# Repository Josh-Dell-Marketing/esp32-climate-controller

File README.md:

# Climate Controller (two ESP32 boards)

Holds a temperature set point and a humidity set point by switching 4 relays: **fan, heater, humidifier, compressor**. The fan speed is set with a 0-10 V signal, and the fan's tach output is watched for a fan fault.

There are two boards joined by a serial cable:

- **Mainboard**: ESP32 NodeMCU WROOM-32 DevKit. Runs the control rules. It reads the AHT20 + BMP280 sensor, switches the relay board, drives the PWM to 0-10 V converter for the fan speed, and reads the fan tach. It keeps the settings in flash, and carries on controlling if the Controller is unplugged.
- **Controller**: ESP32-C3 SuperMini. The user interface: a 1.3" OLED (DST-013) and two rotary encoders with push switches. It shows the readings, the set points, what is running and any fault, and sends your changes to the Mainboard.

More documents:

- The project plan, the control rules and the phases are in **[PLAN.md](PLAN.md)**.
- Picking up the project? Start with **[CLAUDE.md](CLAUDE.md)**.
- Wiring both boards on breadboards and flashing them from Windows 11: **[docs/BENCH_SETUP.md](docs/BENCH_SETUP.md)**.
- **[hardware/](hardware/README.md)** has the relay carrier PCB (KiCad 10), its simulations and a 3D-printable case. These are the Phase 1 **ESP8266** design and do not fit the new Mainboard. They are kept for reference.

**Mains:** a compressor needs a contactor, and a heater needs its own thermal cut-out. See PLAN.md section 1.

## Mainboard pinout (ESP32 NodeMCU WROOM-32)

```
                      +---------------------+
                  EN  | o                 o |  GPIO23
              GPIO36  | o                 o |  GPIO22 ------> sensor SCL
              GPIO39  | o                 o |  GPIO1 (TX0, USB)
 fan tach --> GPIO34  | o                 o |  GPIO3 (RX0, USB)
              GPIO35  | o                 o |  GPIO21 <-----> sensor SDA
 IN3 hum  <-- GPIO32  | o                 o |  GPIO19
 IN4 comp <-- GPIO33  | o                 o |  GPIO18
 fan PWM  <-- GPIO25  | o                 o |  GPIO5
 IN1 fan  <-- GPIO26  | o                 o |  GPIO17 (TX2) ---> Controller RX (GPIO20)
 IN2 heat <-- GPIO27  | o                 o |  GPIO16 (RX2) <--- Controller TX (GPIO21)
              GPIO14  | o                 o |  GPIO4 ----------> RS-485 DE/RE (later)
              GPIO12  | o                 o |  GPIO2
              GPIO13  | o                 o |  GPIO15
                 GND  | o                 o |  GND
 5 V in/out      VIN  | o                 o |  3V3 ------------> sensor VIN, tach pull-up
                      +-------[USB]---------+
```

This is the common 30-pin board. The 38-pin DevKitC has the same GPIOs in a different order, so wire by the GPIO numbers printed on your board.

| GPIO | Connects to | Notes |
|---|---|---|
| 26 | Relay board IN1: **Fan** | |
| 27 | Relay board IN2: **Heater** | |
| 32 | Relay board IN3: **Humidifier** | |
| 33 | Relay board IN4: **Compressor** | |
| VIN (5 V), GND | Relay board VCC, GND | |
| 21 | Sensor SDA | AHT20 (0x38) + BMP280 (0x76/0x77), I2C at 100 kHz |
| 22 | Sensor SCL | |
| 3V3, GND | Sensor VIN, GND | |
| 25 | PWM to 0-10 V converter: PWM input | 1 kHz. Converter GND to Mainboard GND |
| 34 | Fan tach | Input only. **Fit a 10 kΩ pull-up to 3V3** (never 5 V), plus 1 kΩ in series and 10 nF to GND at the pin |
| 17 (TX2) | Controller RX (GPIO 20) | Link, 115200 baud |
| 16 (RX2) | Controller TX (GPIO 21) | |
| 4 | MAX485 DE + /RE (when RS-485 is fitted) | High while sending. Driven even on plain UART, where it is harmless |
| VIN, GND | Controller 5V, GND (in the link cable) | Powers the Controller |

Pins to leave alone: GPIO 0, 2, 5, 12 and 15 (they decide how the chip boots), 6 to 11 (flash), 1 and 3 (USB serial).

**Relay board:** most cheap 4-relay boards switch on when IN is LOW (`RELAY_ACTIVE_LOW = true` in `src/mainboard/config.h`). If a relay will not switch off, or its LED glows faintly, the 3.3 V signal is not quite high enough for the 5 V board. Remove the JD-VCC jumper, power JD-VCC from 5 V, and power VCC from the ESP32's 3V3.

**Fan:** the converter output goes to the fan's 0-10 V input, and its output ground to the fan's 0-10 V reference ground. Check that the fan's 0-10 V input and tach are SELV (isolated from mains) before connecting them. Some converters need a PWM signal of 5 V or more: if yours does not respond to 3.3 V, add a transistor or level shifter. Calibrate it with a meter and set `FAN_PWM_DUTY_AT_0V` / `FAN_PWM_DUTY_AT_10V` in `src/mainboard/config.h`.

## Controller pinout (ESP32-C3 SuperMini)

| GPIO | Connects to | Notes |
|---|---|---|
| 8 | OLED SDA | Strapping pin, held high by the I2C pull-ups |
| 9 | OLED SCK | Strapping pin (BOOT button) |
| 3V3, GND | OLED VDD, GND | |
| 0 | Encoder 1 A (CLK) | Encoder 1: temperature, mode |
| 1 | Encoder 1 B (DT) | |
| 3 | Encoder 1 push (SW) | |
| 4 | Encoder 2 A (CLK) | Encoder 2: humidity, menu |
| 5 | Encoder 2 B (DT) | |
| 10 | Encoder 2 push (SW) | |
| GND | Encoder common (and the switch's other side) | Internal pull-ups are used |
| 21 | Mainboard RX2 (GPIO 16) | Link |
| 20 | Mainboard TX2 (GPIO 17) | |
| 7 | MAX485 DE + /RE (when RS-485 is fitted) | |
| 5V, GND | Mainboard VIN, GND (in the link cable) | |

If your encoders are on a module with a "+" pin (such as the KY-040), connect "+" to **3V3**, not 5 V. GPIO 18/19 are the USB port. GPIO 2 and 6 are spare.

## Link cable

For now this is plain UART over a short cable (4 cores: 5 V, GND, TX, RX, with TX and RX crossed over). For the planned ~10 m run, fit a MAX485-type RS-485 module at each end and use a twisted pair for A/B:

- Each ESP32's TX goes to DI, RX to RO, and the DE and /RE pins (tied together) to GPIO 4 on the Mainboard and GPIO 7 on the Controller. A to A, B to B.
- **The MAX485 is a 5 V chip, and its RO output is 5 V, which the ESP32 inputs cannot take.** Use a 3.3 V part (MAX3485, SP3485) powered from 3V3, or put a divider (for example 1 kΩ / 2 kΩ) between RO and the ESP32 RX pin.
- Fit 120 Ω termination across A/B at both ends of a long cable. Most modules have it on board.
- No firmware change is needed: the link only ever has one side sending at a time, and the DE pin is already driven.

## Build and upload

1. Open this folder in VS Code with the PlatformIO extension.
2. Plug in one board, and pick its environment:
   - Mainboard: `pio run -e mainboard -t upload`
   - Controller: `pio run -e controller -t upload`
3. `pio run` (no `-e`) builds both.
4. Serial monitor at 115200: `pio device monitor -e mainboard` (or `-e controller`).

With both boards plugged in at once, say which port to use. For example, on Windows:

```bash
pio run -e mainboard -t upload --upload-port COM5
```

On Linux the ports are names like `/dev/ttyUSB0` (Mainboard) and `/dev/ttyACM0` (Controller).

The SuperMini flashes over its own USB port. If it will not connect, hold **BOOT**, tap **RESET**, release BOOT and upload again. After that, press RESET to start the new firmware.

The WROOM-32 DevKit needs a CP210x or CH340 USB driver on Windows, depending on the board. If an upload hangs at "Connecting...", hold its **BOOT** button until the upload starts.

## Using the Controller

**Home screen:** temperature and humidity (large), the set points, the mode, the loads that are running, and a bottom line with the fan speed and RPM, the pressure, or a fault.

| Control | What it does |
|---|---|
| Turn encoder 1 | Temperature set point (0.1 °C steps) |
| Push encoder 1 | Next mode: Off, Auto, Manual |
| Turn encoder 2 | Humidity set point (1 % steps) |
| Long-push encoder 2 | Settings menu |

A value you are changing is shown inverted. It is sent to the Mainboard once the knob has been still for 1 s, and goes back to normal when the Mainboard accepts it.

**Settings menu:** turn encoder 2 to choose an item, and turn encoder 1 to change it. Push either encoder on **Clear fan fault** or **Exit**. Long-push encoder 2 to go back, or leave it alone for 60 s. The items are:

- Bands and the fan settings: fan mode, speed, run-on, and the fan fault RPM (0 turns the check off), spin-up and delay.
- Compressor times and sensor offsets.
- The manual relay switches (only shown in Manual mode).
- Real or simulated sensor. In Sim, the simulated temperature, humidity, "room reacts" and sensor fault are shown too.

**Faults:** SENSOR FAULT and FAN FAULT take over the screen until you push either encoder. They then stay on the bottom line while they last. A fan fault is latched: clear it from the menu once the fan is working again. If the Controller hears nothing from the Mainboard for 5 s it shows **NO LINK TO MAINBOARD**. The Mainboard keeps controlling with its saved settings.

The simulated sensor is never saved: the Mainboard always starts on the real sensor after a reset.

## Mainboard serial commands (115200 baud, USB)

For bench testing without the Controller. Type `help` for the list.

```
status | settings | help
mode off|auto|manual
sensor real|sim
temp <C> | hum <%RH>        simulated reading (switches to the simulated sensor)
react on|off | fault on|off
relay <1-4> on|off           Manual mode only
clearfault
set <name> <value>           any name from "settings", e.g. set tempset 21.5
```

## Files

```
PLAN.md                        Project plan, control rules, pin plan, phases
platformio.ini                 Build environments: mainboard, controller
include/link_protocol.h        Link messages, shared by both firmwares
src/mainboard/main.cpp         Mainboard: relays, fan, link, serial commands
src/mainboard/climate_control.*  Control rules and fan fault (plain C++, no Arduino code)
src/mainboard/sensor.*         AHT20 + BMP280
src/mainboard/fan.*            Fan PWM (0-10 V) and tach
src/mainboard/storage.*        Saves settings to flash
src/mainboard/sim_room.h       Simulated sensor and room
src/mainboard/config.h         Mainboard pins and timings
src/controller/main.cpp        Controller: display, menus, link
src/controller/input.h         Encoders and push buttons
src/controller/config.h        Controller pins and timings
tools/host-test/               Tests of the control rules and link framing, run on a PC
```

The control rules can be tested on a PC without a board (needs `g++`):

```bash
g++ -std=c++17 -Isrc/mainboard -Iinclude tools/host-test/test_control.cpp src/mainboard/climate_control.cpp -o test_control && ./test_control
```

The Phase 1 firmware (ESP8266, web page, WiFi, OTA) was removed. The last commit with it is `65d825e`.

## License

- Firmware, scripts and documentation: [MIT](LICENSE).
- Hardware (everything in `hardware/`: the KiCad design files, generator scripts, simulations and case CAD): [CERN-OHL-P-2.0](hardware/LICENSE), the permissive CERN Open Hardware Licence. You may use, change, make and sell it. Keep the licence notice with any copies of the design files.

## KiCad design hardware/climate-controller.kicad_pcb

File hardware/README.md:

# Climate Controller – Relay Carrier PCB

> **Status: Phase 1 design, on hold.** This board was designed for the original single-board version (ESP8266 NodeMCU v2 + SHT31-D). The project now uses an ESP32 WROOM-32 Mainboard with an AHT20 + BMP280 sensor, a PWM to 0-10 V fan speed output, a fan tach input and a link to a separate Controller board (see [PLAN.md](../PLAN.md)). This PCB does not fit that, and the `nodemcuv2-pcb` firmware environment it needs has been removed. The last commit with that firmware is `65d825e`. Whether to rework this board for the ESP32 or to use an off-the-shelf relay board is an open item in PLAN.md Phase 5. Everything below describes the board as designed.

A 2-layer, 90 × 86 mm through-hole carrier board for the climate controller. It has:

- 4 × SRD-05VDC-SL-C relays: fan, humidifier, compressor and heater.
- A plug-in NodeMCU v2 (ESP8266), so you keep USB programming and the existing firmware pins.
- A JST connector for the SHT31-D sensor.
- 5 V DC input with a resettable fuse and reverse-polarity protection.

Everything here is generated from **`gen/design.py`**: parts, values, connections and placement. Change the design there and rebuild. Don't hand-edit the `.kicad_sch` / `.kicad_pcb` and then rebuild, because the rebuild overwrites them. You can still open and inspect them in KiCad 10.

| File | What it is |
|---|---|
| `climate-controller.kicad_pro/.kicad_sch/.kicad_pcb` | The KiCad 10 project. Open the `.kicad_pro` in KiCad |
| `climate-controller.kicad_dru` | Custom DRC rules: mains clearance and creepage |
| `lib/` | Project symbol and footprint for the NodeMCU, plus a simple 3D model |
| `gen/` | Generator: `design.py` (single source), `make_sch.py`, `make_pcb.py`, `router.py`, `make_pro.py` |
| `build.ps1` | Rebuilds everything and runs ERC/DRC. `-Fab` also writes manufacturing files |
| `sim/` | SPICE simulations (ngspice): `SIM_REPORT.md`, plots, `run_sim.py` |
| `case/` | 3D-printable enclosure (CadQuery): see `case/CASE.md` |
| `build/` | Generated: renders, ERC/DRC reports, `fab/` (Gerbers, drill, BOM, PDFs, STEP). Not in git |

## Rebuild and check

```
powershell -ExecutionPolicy Bypass -File hardware\build.ps1 -Fab
```

This takes about 1 minute and needs KiCad 10 in `C:\Program Files\KiCad\10.0`. It writes the schematic, runs ERC, places and routes the PCB, pours ground, runs DRC with the schematic-parity check, renders images, and exports the manufacturing files.

Results of the current design:

| Check | Result |
|---|---|
| ERC | 0 errors, 0 warnings |
| DRC | 0 errors, 0 unconnected items, 0 schematic/PCB differences. The 91 warnings are silkscreen cosmetics, such as text overlapping outlines |
| Mains → low-voltage clearance (rule ≥ 3.0 mm) | **3.70 mm** minimum |
| Mains → low-voltage creepage (rule ≥ 4.0 mm) | **4.83 mm** minimum, using routed slots around each relay's COM pin |
| Mains → mains, between COM/NO/NC (rule ≥ 2.0 mm) | 2.78 mm minimum. This is set by the 5.08 mm terminal pitch |
| Mains → mounting screws (rule ≥ 3.0 mm) | 5.12 mm minimum |

Each minimum was measured with KiCad's DRC engine. I also checked that the rules really are enforced: setting them to 20 mm on a scratch copy produced hundreds of violations. KiCad silently ignores a rule condition written as `!B.hasNetclass('Mains')`, so `gen/make_pro.py` uses `B.NetClass != 'Mains'`.

## Circuit

- **Relay driver (×4):** GPIO → 1 kΩ → BC337-40, with 4.7 kΩ base-to-emitter so the relay stays off while the ESP8266 boots. The coil runs from +5 V with a 1N4148 flyback diode. A red LED + 1 kΩ across the coil shows when the relay is on. **The relays are active HIGH**, so the firmware must have `RELAY_ACTIVE_LOW = false` (this was the Phase 1 `nodemcuv2-pcb` build).
- **Channels, left to right:** 1 FAN (D0), 2 HUMIDIFIER (D5), 3 COMPRESSOR (D6), 4 HEATER (D7). These match the Phase 1 (ESP8266) firmware pins. The order follows the NodeMCU pin order so the traces don't cross.
- **Outputs:** each relay has a 3-way screw terminal, NC / COM / NO from left to right.
- **Power:** J1 5 V DC → F1 PTC fuse → D5 1N5819 (reverse protection) → +5V → relays and NodeMCU VIN. **Use a 5.1–5.25 V, ≥ 1 A supply.** The fuse and diode drop about 0.45 V, and the NodeMCU's 3.3 V regulator needs about 4.4 V in. The simulation shows a bare 5.00 V supply leaves only 70 mV of headroom on the regulator input.
- **Sensor:** J6 (JST-XH 4-pin) is wired 3V3, GND, SCL, SDA, matching most SHT31-D breakouts. R14/R15 are 4.7 kΩ pull-ups. J7 is a spare I2C header. Run I2C at 100 kHz.
- **USB:** with the NodeMCU on USB and no 5 V supply, the relays still work, powered through the NodeMCU's own diode. D5 stops that power flowing back into J1. With all 4 relays on, peaks reach about 0.57 A, which is over a USB 2.0 port's 500 mA. Use the 5 V supply for anything more than a quick test.

## Simulation summary (`sim/SIM_REPORT.md`)

These were run in ngspice with manufacturer SPICE models. A coil inductance of 50–500 mH was swept, and the results don't depend on it.

| Check | Result |
|---|---|
| GPIO current | 2.4 mA (limit 12 mA) |
| Transistor Vce(sat) | 55 mV worst case |
| Coil voltage at 4.5 V supply | 4.45 V (must-operate 3.75 V) |
| Turn-off spike | 5.8 V with the flyback diode (about 50 V and avalanche without it) |
| Relay held off during boot | Yes, with the 4.7 kΩ pull-downs, even with a 30 kΩ internal pull-up enabled (10 kΩ failed that case) |
| +5 V rail at 5.0 V input | ≥ 4.47 V (typical diode). With a 4.75 V input the 3.3 V regulator is short of headroom, hence the 5.1–5.25 V supply |
| I2C rise time | 0.4–0.8 µs at 100–200 pF (passes 100 kHz). For a long sensor cable (≈400 pF), fit 2.2 kΩ pull-ups |
| Relay contact traces | 2 mm on both layers: about 5 °C rise at 5 A, 16 °C at 8 A. **This board is rated 5 A per channel** |

## Ordering the PCB

Upload `build/fab/climate-controller-gerbers.zip` to any PCB maker (for example JLCPCB, PCBWay or Aisler) with these settings:

- 2 layers, FR4, 1.6 mm, 1 oz copper (2 oz is optional), HASL or ENIG, any colour.
- **Board outline includes routed slots.** Four U-shaped 1 mm slots around the relay COM pins are on the Edge.Cuts layer. Most makers mill these at no extra cost; check that they appear in the maker's Gerber preview.

## Parts (BOM)

The full BOM is in `build/fab/climate-controller-bom.csv`.

| Refs | Qty | Part | Notes |
|---|---|---|---|
| K1–K4 | 4 | Songle SRD-05VDC-SL-C | 5 V coil, 10 A contacts. **5 A max on this board** |
| Q1–Q4 | 4 | BC337-40, TO-92 | Pinout C-B-E |
| D1–D4 | 4 | 1N4148 | Flyback, cathode band to +5V |
| D5 | 1 | 1N5819 | Reverse protection |
| D6–D9 / D10 | 4 / 1 | 3 mm LED, red / green | Relay on / power |
| R1–R4, R9–R13 | 9 | 1 kΩ ¼ W | |
| R5–R8, R14, R15 | 6 | 4.7 kΩ ¼ W | |
| C1 | 1 | 470 µF 10 V electrolytic, 8 mm, 3.5 mm pitch | |
| C2, C3 | 2 | 100 nF ceramic, 5 mm pitch | |
| F1 | 1 | Bourns MF-RHT100 PTC (about 1 A hold) | Check the hold current on the datasheet before ordering. Any radial PTC of about 1 A hold, ≥ 6 V, with 5.1 mm pitch fits |
| J1 | 1 | Phoenix MKDS 1,5/2-5,08 (or any 5.08 mm 2-way screw terminal) | |
| J2–J5 | 4 | Phoenix MKDS 1,5/3-5,08 (or any 5.08 mm 3-way screw terminal) | Wire entry faces the board edge |
| J6 | 1 | JST B4B-XH-A + housing XHP-4 + crimps | Sensor cable |
| J7 | 1 | 1×4 2.54 mm pin header | Optional |
| U1 | 2 | 1×15 2.54 mm female header | The NodeMCU v2 plugs in here |
| – | 4 | M3 screws | Mounting |

## Assembly

1. **Check your NodeMCU first.** This board is for the v2 "Amica" (CP2102 USB chip) with **22.86 mm (0.9 in) between the pin rows**. The wider "LoLin v3" (27.9 mm) will not fit.
2. Solder the lowest parts first: resistors, diodes, then LEDs and transistors (flat face as on the silkscreen), C2/C3, the sockets, C1, F1, the terminals and JST connector, and finally the relays.
3. **Bring-up, without the NodeMCU:**
   - Apply 5.1 V to J1. The green LED should light.
   - Check about 4.6–4.7 V between the +5V and GND pins of the sockets (U1 pin 15 VIN and pin 14 GND).
   - Touch a 1 kΩ resistor from 3.3 V to each relay's base resistor (R1–R4, GPIO side). The relay should click and its red LED light.
4. Plug in the NodeMCU with the USB end at the board edge. Flash the Phase 1 firmware (commit `65d825e`) with `pio run -e nodemcuv2-pcb -t upload`.
5. Test each relay in the web page's **Manual** mode before connecting any load.

## Safety

- The relay contact area (top of the board, "DANGER MAINS") can be at mains voltage. Mains wiring must be done by a competent person, in an earthed or double-insulated enclosure, with suitable fusing on each load.
- 5 A per channel. Drive the **compressor through a contactor** (AC-3 rated), and do the same for any heater over about 1 kW. Fit the heater's own thermal cut-out.
- A 3D-printed case is fine for development. For a permanent mains installation, use a flame-retardant (UL94 V-0) material or a commercial enclosure.

## License

The hardware design in this folder is licensed under the [CERN Open Hardware Licence Version 2 – Permissive](LICENSE) (CERN-OHL-P-2.0). Copyright (c) 2026 Josh-Dell-Marketing and contributors.

Third-party material used in the design keeps its own terms:
- Symbols, footprints and 3D models from the KiCad libraries (embedded in the `.kicad_sch` / `.kicad_pcb` and referenced by the STEP export) are from the KiCad Libraries Team, under CC-BY-SA 4.0 with an exception that allows them to be used in designs under any licence.
- The SPICE models in `sim/models/` come from the manufacturers' published models (NXP/Nexperia BC337-40, onsemi 1N4148 and 1N5819), as noted in each file. They are included for simulation only.

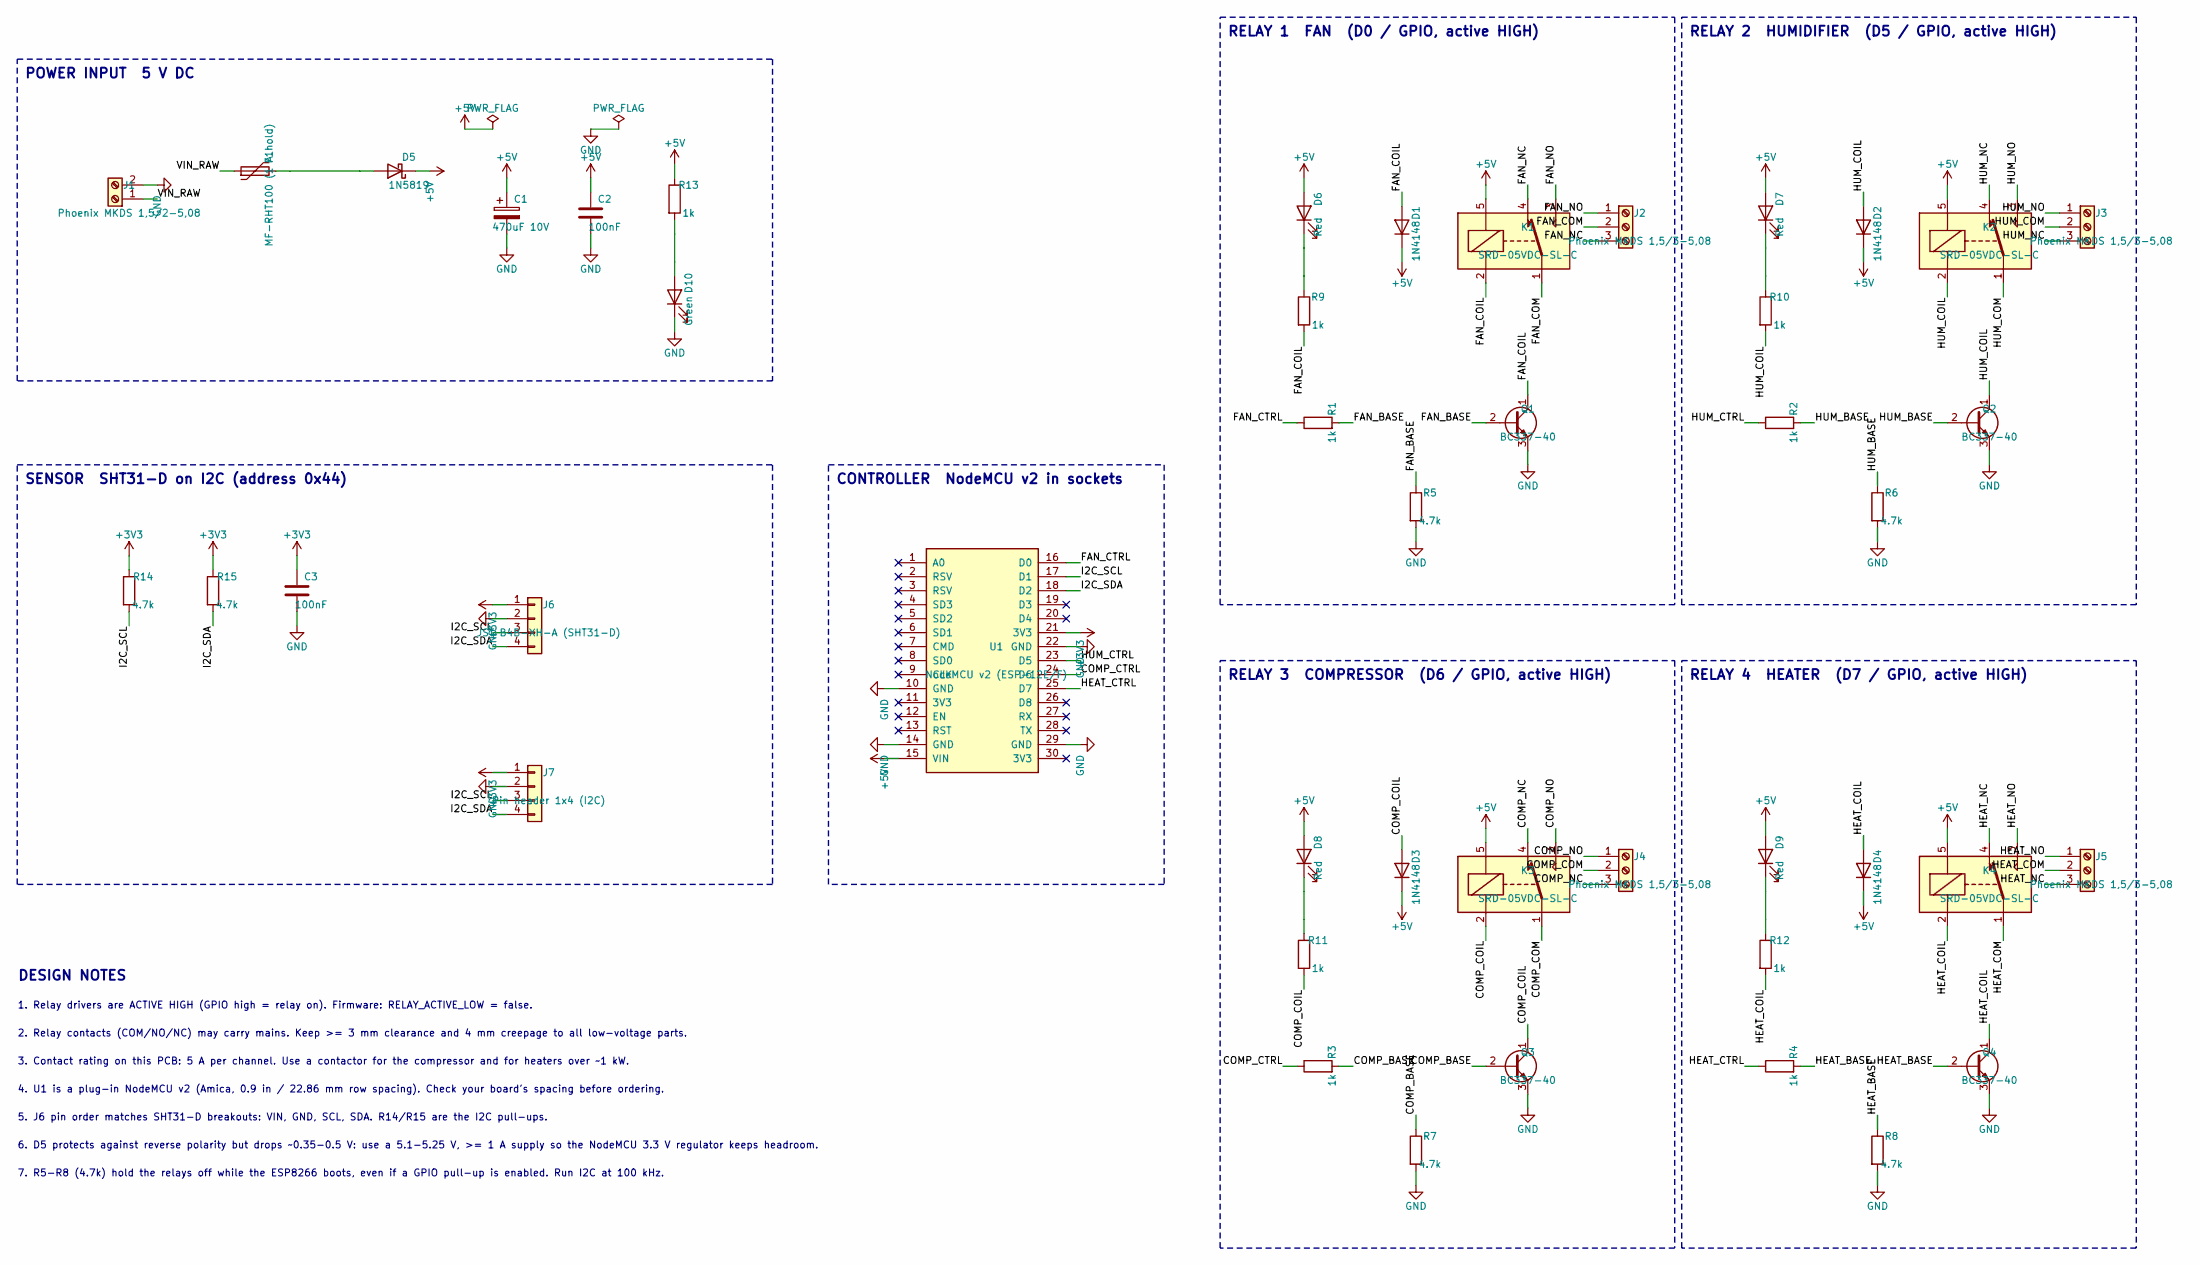
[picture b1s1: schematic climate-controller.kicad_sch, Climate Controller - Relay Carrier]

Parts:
C1: 470uF 10V; CP_Radial_D8.0mm_P3.50mm
C2, C3: 100nF; C_Disc_D5.0mm_W2.5mm_P5.00mm
D1, D2, D3, D4: 1N4148; D_DO-35_SOD27_P7.62mm_Horizontal
D5: 1N5819; D_DO-41_SOD81_P10.16mm_Horizontal
D6, D7, D8, D9: Red; LED_D3.0mm
D10: Green; LED_D3.0mm
F1: MF-RHT100 (1 A hold); Fuse_Bourns_MF-RHT100
J1: Phoenix MKDS 1,5/2-5,08; TerminalBlock_Phoenix_MKDS-1,5-2-5.08_1x02_P5.08mm_Horizont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
J2, J3, J4, J5: Phoenix MKDS 1,5/3-5,08; TerminalBlock_Phoenix_MKDS-1,5-3-5.08_1x03_P5.08mm_Horizont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
J6: JST B4B-XH-A (SHT31-D); JST_XH_B4B-XH-A_1x04_P2.50mm_Vertical
J7: Pin header 1x4 (I2C); PinHeader_1x04_P2.54mm_Vertical
K1, K2, K3, K4: SRD-05VDC-SL-C; Relay_SPDT_SANYOU_SRD_Series_Form_C
Q1, Q2, Q3, Q4: BC337-40; TO-92_Inline_Wide
R1, R2, R3, R4, R9, R10, R11, R12, R13: 1k; R_Axial_DIN0207_L6.3mm_D2.5mm_P7.62mm_Horizontal
R5, R6, R7, R8, R14, R15: 4.7k; R_Axial_DIN0207_L6.3mm_D2.5mm_P7.62mm_Horizontal
U1: NodeMCU v2 (ESP-12E/F); NodeMCU_v2_Socket

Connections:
+3V3: C3.1, J6.1, J7.1, R14.1, R15.1, U1.21 (3V3)
+5V: C1.1, C2.1, D1.1 (K), D2.1 (K), D3.1 (K), D4.1 (K), D5.1 (K), D6.2 (A), D7.2 (A), D8.2 (A), D9.2 (A), K1.5, K2.5, K3.5, K4.5, R13.1, U1.15 (VIN)
/COMP_BASE: Q3.2 (B), R3.2, R7.1
/COMP_COIL: D3.2 (A), K3.2, Q3.1 (C), R11.2
/COMP_COM: J4.2, K3.1
/COMP_CTRL: R3.1, U1.24 (D6)
/COMP_NC: J4.3, K3.4
/COMP_NO: J4.1, K3.3
/FAN_BASE: Q1.2 (B), R1.2, R5.1
/FAN_COIL: D1.2 (A), K1.2, Q1.1 (C), R9.2
/FAN_COM: J2.2, K1.1
/FAN_CTRL: R1.1, U1.16 (D0)
/FAN_NC: J2.3, K1.4
/FAN_NO: J2.1, K1.3
/HEAT_BASE: Q4.2 (B), R4.2, R8.1
/HEAT_COIL: D4.2 (A), K4.2, Q4.1 (C), R12.2
/HEAT_COM: J5.2, K4.1
/HEAT_CTRL: R4.1, U1.25 (D7)
/HEAT_NC: J5.3, K4.4
/HEAT_NO: J5.1, K4.3
/HUM_BASE: Q2.2 (B), R2.2, R6.1
/HUM_COIL: D2.2 (A), K2.2, Q2.1 (C), R10.2
/HUM_COM: J3.2, K2.1
/HUM_CTRL: R2.1, U1.23 (D5)
/HUM_NC: J3.3, K2.4
/HUM_NO: J3.1, K2.3
/I2C_SCL: J6.3, J7.3, R14.2, U1.17 (D1)
/I2C_SDA: J6.4, J7.4, R15.2, U1.18 (D2)
/VIN_RAW: F1.1, J1.1
GND: C1.2, C2.2, C3.2, D10.1 (K), J1.2, J6.2, J7.2, Q1.3 (E), Q2.3 (E), Q3.3 (E), Q4.3 (E), R5.2, R6.2, R7.2, R8.2, U1.10 (GND), U1.14 (GND), U1.22 (GND), U1.29 (GND)
unnamed: D5.2 (A), F1.2
unnamed: D6.1 (K), R9.1
unnamed: D7.1 (K), R10.1
unnamed: D8.1 (K), R11.1
unnamed: D9.1 (K), R12.1
unnamed: D10.2 (A), R13.2

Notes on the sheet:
4. U1 is a plug-in NodeMCU v2 (Amica, 0.9 in / 22.86 mm row spacing). Check your board's spacing before ordering.
RELAY 3 COMPRESSOR (D6 / GPIO, active HIGH)
SENSOR SHT31-D on I2C (address 0x44)
5. J6 pin order matches SHT31-D breakouts: VIN, GND, SCL, SDA. R14/R15 are the I2C pull-ups.
CONTROLLER NodeMCU v2 in sockets
7. R5-R8 (4.7k) hold the relays off while the ESP8266 boots, even if a GPIO pull-up is enabled. Run I2C at 100 kHz.
3. Contact rating on this PCB: 5 A per channel. Use a contactor for the compressor and for heaters over ~1 kW.
RELAY 4 HEATER (D7 / GPIO, active HIGH)
2. Relay contacts (COM/NO/NC) may carry mains. Keep >= 3 mm clearance and 4 mm creepage to all low-voltage parts.
DESIGN NOTES
POWER INPUT 5 V DC
1. Relay drivers are ACTIVE HIGH (GPIO high = relay on). Firmware: RELAY_ACTIVE_LOW = false.
RELAY 1 FAN (D0 / GPIO, active HIGH)
6. D5 protects against reverse polarity but drops ~0.35-0.5 V: use a 5.1-5.25 V, >= 1 A supply so the NodeMCU 3.3 V regulator keeps headroom.
RELAY 2 HUMIDIFIER (D5 / GPIO, active HIGH)

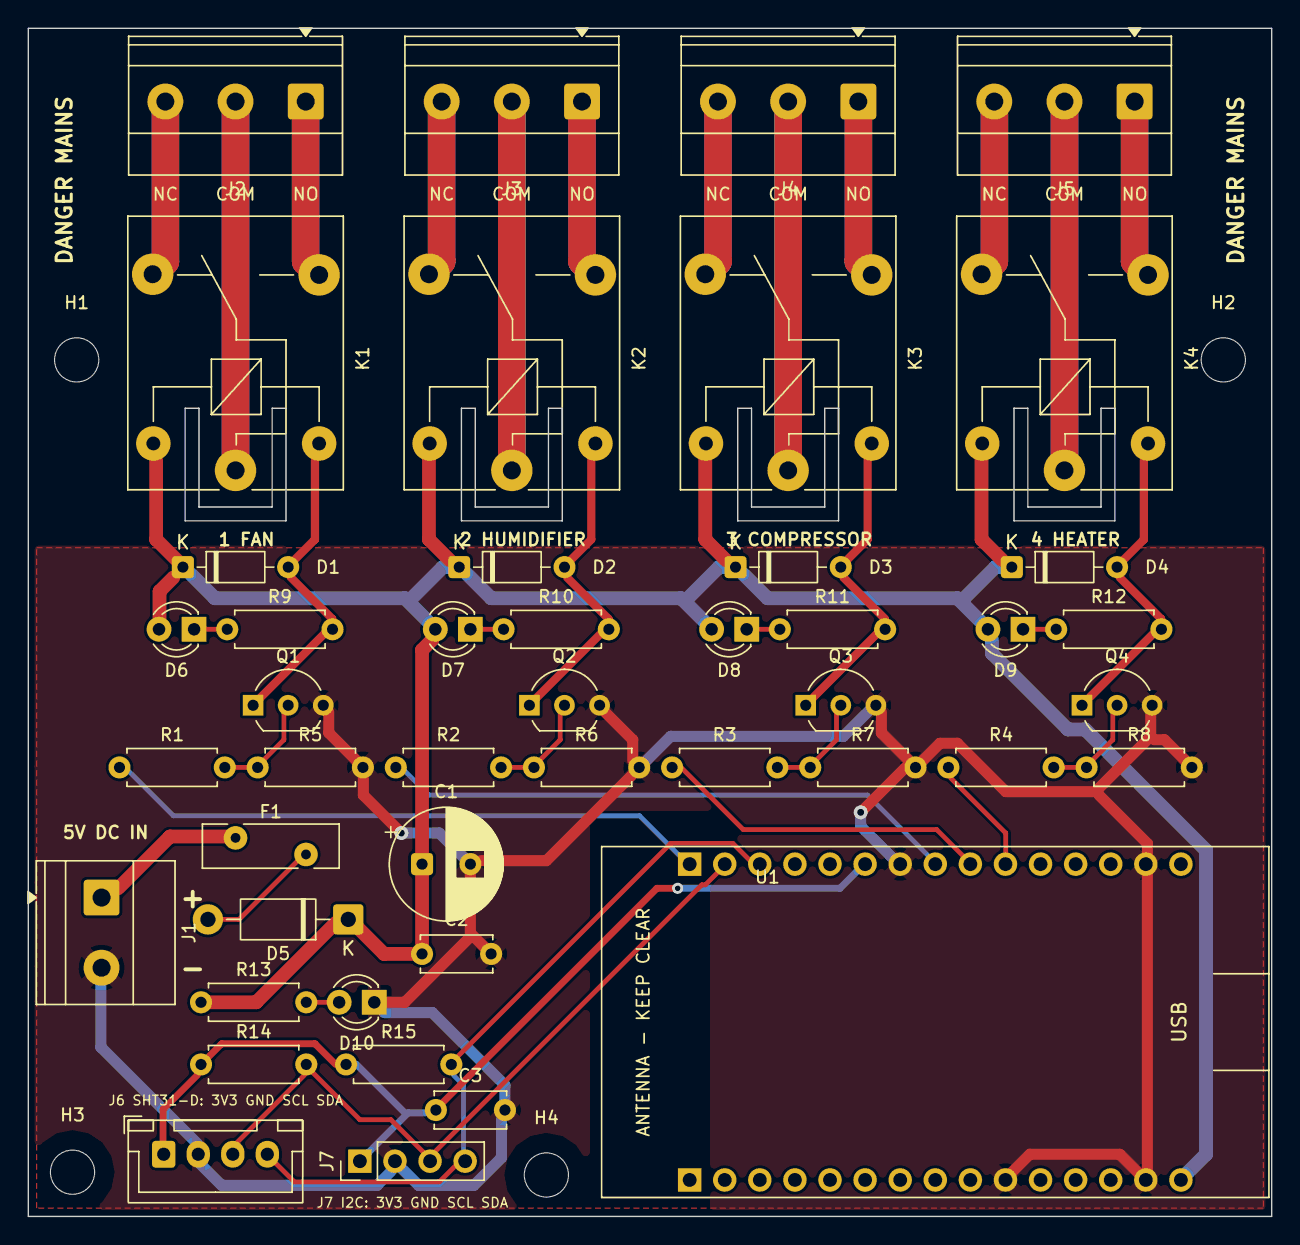
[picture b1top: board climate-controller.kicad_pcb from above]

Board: 2 copper layers, 90.0 x 86.0 mm, 49 parts (0 on the bottom side), 36 nets.

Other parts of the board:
H1, H2, H3, H4: M3; MountingHole_3.2mm_M3
